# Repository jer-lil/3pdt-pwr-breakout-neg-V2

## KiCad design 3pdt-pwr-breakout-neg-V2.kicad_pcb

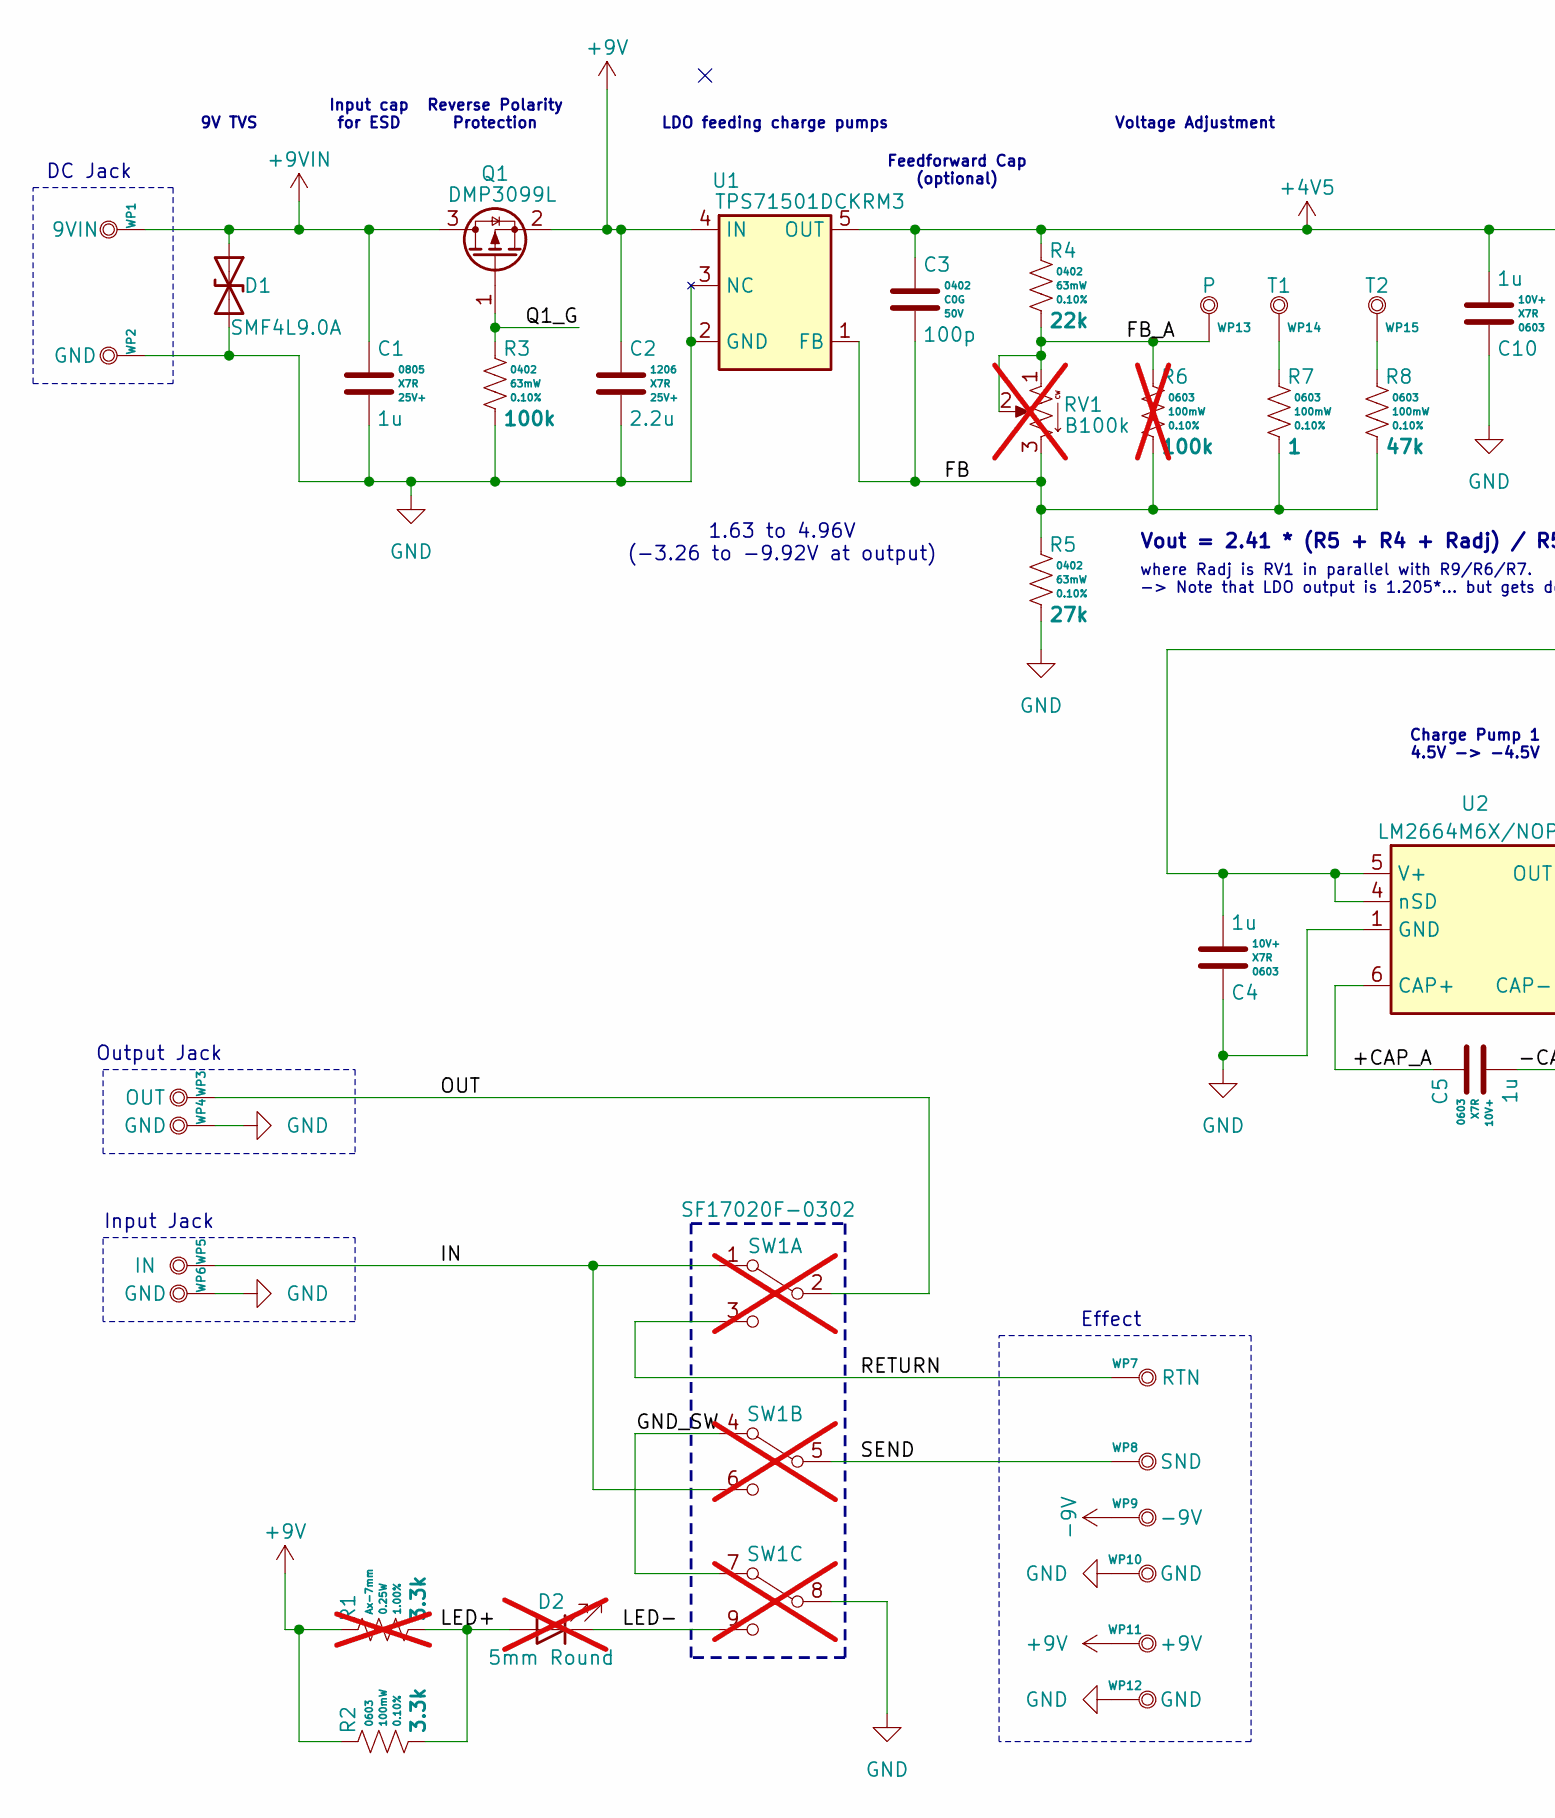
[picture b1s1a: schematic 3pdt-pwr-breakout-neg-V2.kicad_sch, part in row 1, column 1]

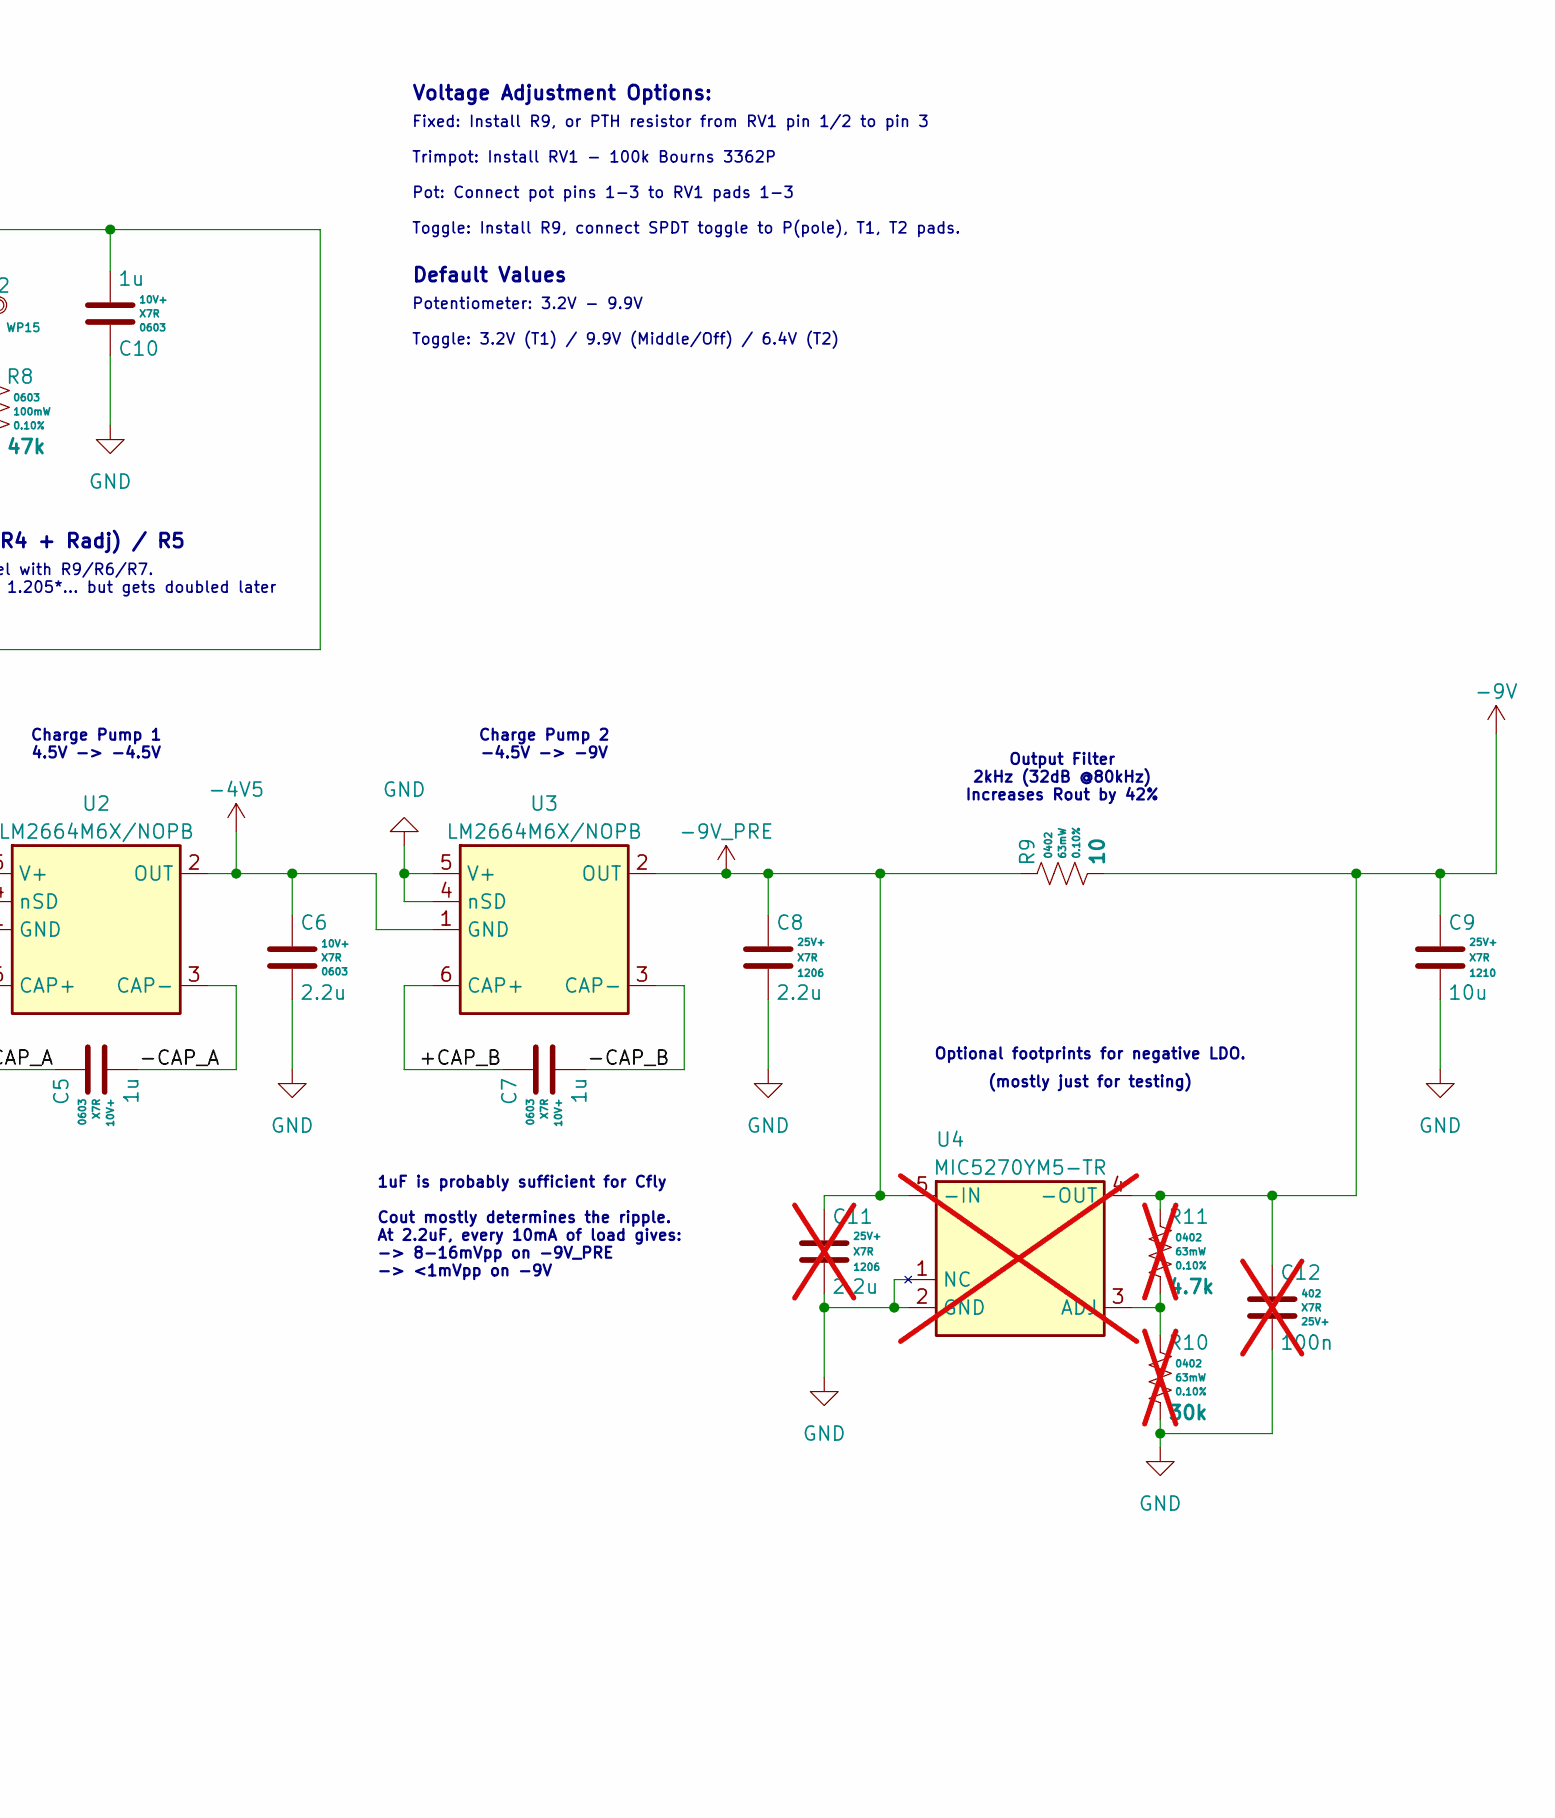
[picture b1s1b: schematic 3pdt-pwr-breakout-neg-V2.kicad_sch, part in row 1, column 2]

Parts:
C1: 1u; C_0805_2012Metric; Voltage 25V+; Tolerance 10%; MPN C0805C105K3RACTU
C2, C8: 2.2u; C_1206_3216Metric; Voltage 25V+; Tolerance 10%; MPN C1206C225K3RACTU
C3: 100p; C_0402_1005Metric; Voltage 50V; Tolerance +/-2%; MPN GRM1555C1H100GA01D
C4, C5, C7, C10: 1u; C_0603_1608Metric; Voltage 10V+; Tolerance 10%; MPN C0603C105K8RACTU
C6: 2.2u; C_0603_1608Metric; Voltage 10V+; Tolerance 10%; MPN C0603C225K8RACTU
C9: 10u; C_1210_3225Metric; Voltage 25V+; Tolerance 10%; MPN C1210C106K3RACTU
C11: 2.2u; C_1206_3216Metric; Voltage 25V+; Tolerance 10%; MPN C1206C225K3RACTU; not fitted
C12: 100n; C_0402_1005Metric; Voltage 25V+; Tolerance 10%; MPN C0402C104K3RACTU; not fitted
D1: SMF4L9.0A; D_SOD-123F; MPN SMF4L9.0A
D2: LED_PTH; LED_D5.0mm_Standoff; not fitted
Q1: DMP3099L; SOT-23; MPN DMP3099L
R1: 3.3k; R_Axial_DIN0207_L6.3mm_D2.5mm_P7.5mm_Horizontal; Tolerance 1.00%; Voltage 250V; MPN MFR-25FBF52-3K3; not fitted
R2: 3.3k; R_0603_1608Metric; Tolerance 0.10%; Voltage 75V; MPN RT0603BRD073K3L
R3: 100k; R_0402_1005Metric; Tolerance 0.10%; Voltage 50V; MPN RT0402BRD07100KL
R4: 22k; R_0402_1005Metric; Tolerance 0.10%; Voltage 50V; MPN RT0402BRD0722KL
R5: 27k; R_0402_1005Metric; Tolerance 0.10%; Voltage 50V; MPN RT0402BRD0727KL
R6: 100k; R_0603_1608Metric; Tolerance 0.10%; Voltage 75V; MPN RT0603BRD07100KL; not fitted
R7: 1; R_0603_1608Metric; Tolerance 0.10%; Voltage 75V; MPN RT0603BRD071RL
R8: 47k; R_0603_1608Metric; Tolerance 0.10%; Voltage 75V; MPN RT0603BRD0747KL
R9: 10; R_0402_1005Metric; Tolerance 0.10%; Voltage 50V; MPN RT0402BRD0710RL
R10: 30k; R_0402_1005Metric; Tolerance 0.10%; Voltage 50V; MPN RT0402BRD0730KL; not fitted
R11: 4.7k; R_0402_1005Metric; Tolerance 0.10%; Voltage 50V; MPN RT0402BRD074K7L; not fitted
RV1: B100k; Potentiometer_Bourns_3362P_Vertical; MPN 3362P-1-104LF; not fitted
SW1: SW_3PDT; SW_STOMP_3PDT; MPN SF17020F-0302; not fitted
U1: TPS71501DCKRM3; SOT-353_SC-70-5; Voltage ADJ; MPN TPS71501DCKRM3
U2, U3: LM2664M6X/NOPB; SOT-23-6; Voltage Ratiometric; MPN LM2664M6X/NOPB
U4: MIC5270YM5-TR; SOT-23-5; Voltage ADJ; MPN MIC5270YM5-TR; not fitted
WP1: 9VIN; WirePad_H0.95mm_22-24AWG
WP2, WP4, WP6, WP10, WP12: GND; WirePad_H0.95mm_22-24AWG
WP3: OUT; WirePad_H0.95mm_22-24AWG
WP5: IN; WirePad_H0.95mm_22-24AWG
WP7: RTN; WirePad_H0.95mm_22-24AWG
WP8: SND; WirePad_H0.95mm_22-24AWG
WP9: -9V; WirePad_H0.95mm_22-24AWG
WP11: +9V; WirePad_H0.95mm_22-24AWG
WP13: P; WirePad_H0.95mm_22-24AWG
WP14: T1; WirePad_H0.95mm_22-24AWG
WP15: T2; WirePad_H0.95mm_22-24AWG

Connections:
+4V5: C3.1, C4.2, C10.2, R4.1, U1.5 (OUT), U2.4 (nSD), U2.5 (V+)
+9V: C2.1, Q1.2 (S), R1.1, R2.1, U1.4 (IN), WP11.1
+9VIN: C1.1, D1.1 (A1), Q1.3 (D), WP1.1
-4V5: C6.2, U2.2 (OUT), U3.1 (GND)
-9V: C9.1, C12.1, R9.2, R11.1, U4.4 (-OUT), WP9.1
-9V_PRE: C8.1, C11.1, R9.1, U3.2 (OUT), U4.5 (-IN)
/+CAP_A: C5.1, U2.6 (CAP+)
/+CAP_B: C7.1, U3.6 (CAP+)
/-CAP_A: C5.2, U2.3 (CAP-)
/-CAP_B: C7.2, U3.3 (CAP-)
/FB: C3.2, R5.1, R6.2, R7.2, R8.2, RV1.3, U1.1 (FB)
/FB_A: R4.2, R6.1, RV1.1, RV1.2, WP13.1
/GND_SW: SW1.4 (A), SW1.7 (A)
/IN: SW1.1 (A), SW1.6 (C), WP5.1
/LED+: D2.2 (A), R1.2, R2.2
/LED-: D2.1 (K), SW1.9 (C)
/OUT: SW1.2 (B), WP3.1
/Q1_G: Q1.1 (G), R3.1
/RETURN: SW1.3 (C), WP7.1
/SEND: SW1.5 (B), WP8.1
GND: C1.2, C2.2, C4.1, C6.1, C8.2, C9.2, C10.1, C11.2, C12.2, D1.2 (A2), R3.2, R5.2, R10.2, SW1.8 (B), U1.2 (GND), U1.3 (NC), U2.1 (GND), U3.4 (nSD), U3.5 (V+), U4.1 (NC), U4.2 (GND), WP2.1, WP4.1, WP6.1, WP10.1, WP12.1
unnamed: R7.1, WP14.1
unnamed: R8.1, WP15.1
unnamed: R10.1, R11.2, U4.3 (ADJ)

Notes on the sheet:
Default Values
Optional footprints for negative LDO.
Voltage Adjustment
where Radj is RV1 in parallel with R9/R6/R7. -> Note that LDO output is 1.205*... but gets doubled later
Reverse Polarity Protection
Effect
DC Jack
Input cap for ESD
Feedforward Cap (optional)
Voltage Adjustment Options:
Fixed: Install R9, or PTH resistor from RV1 pin 1/2 to pin 3 Trimpot: Install RV1 - 100k Bourns 3362P Pot: Connect pot pins 1-3 to RV1 pads 1-3 Toggle: Install R9, connect SPDT toggle to P(pole), T1, T2 pads.
9V TVS
1.63 to 4.96V (-3.26 to -9.92V at output)
Vout = 2.41 * (R5 + R4 + Radj) / R5
LDO feeding charge pumps
Charge Pump 1 4.5V -> -4.5V
Output Filter 2kHz (32dB @80kHz) Increases Rout by 42%
Charge Pump 2 -4.5V -> -9V
1uF is probably sufficient for Cfly Cout mostly determines the ripple. At 2.2uF, every 10mA of load gives: -> 8-16mVpp on -9V_PRE -> <1mVpp on -9V
Potentiometer: 3.2V - 9.9V Toggle: 3.2V (T1) / 9.9V (Middle/Off) / 6.4V (T2)
Output Jack
Input Jack
(mostly just for testing)

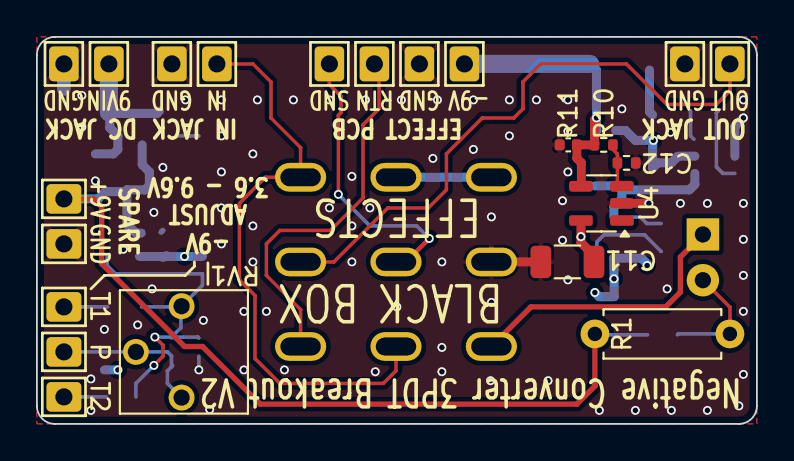
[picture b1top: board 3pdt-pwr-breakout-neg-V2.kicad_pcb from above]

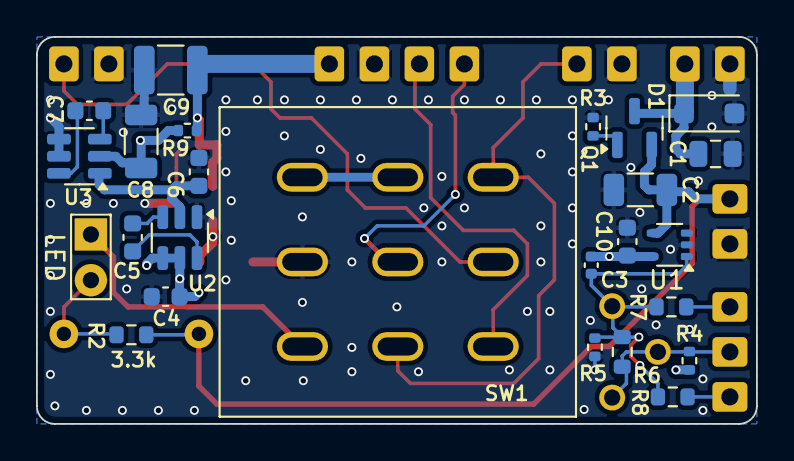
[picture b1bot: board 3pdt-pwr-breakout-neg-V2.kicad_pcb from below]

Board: 4 copper layers, 40.0 x 21.5 mm, 47 parts (25 on the bottom side), 24 nets.

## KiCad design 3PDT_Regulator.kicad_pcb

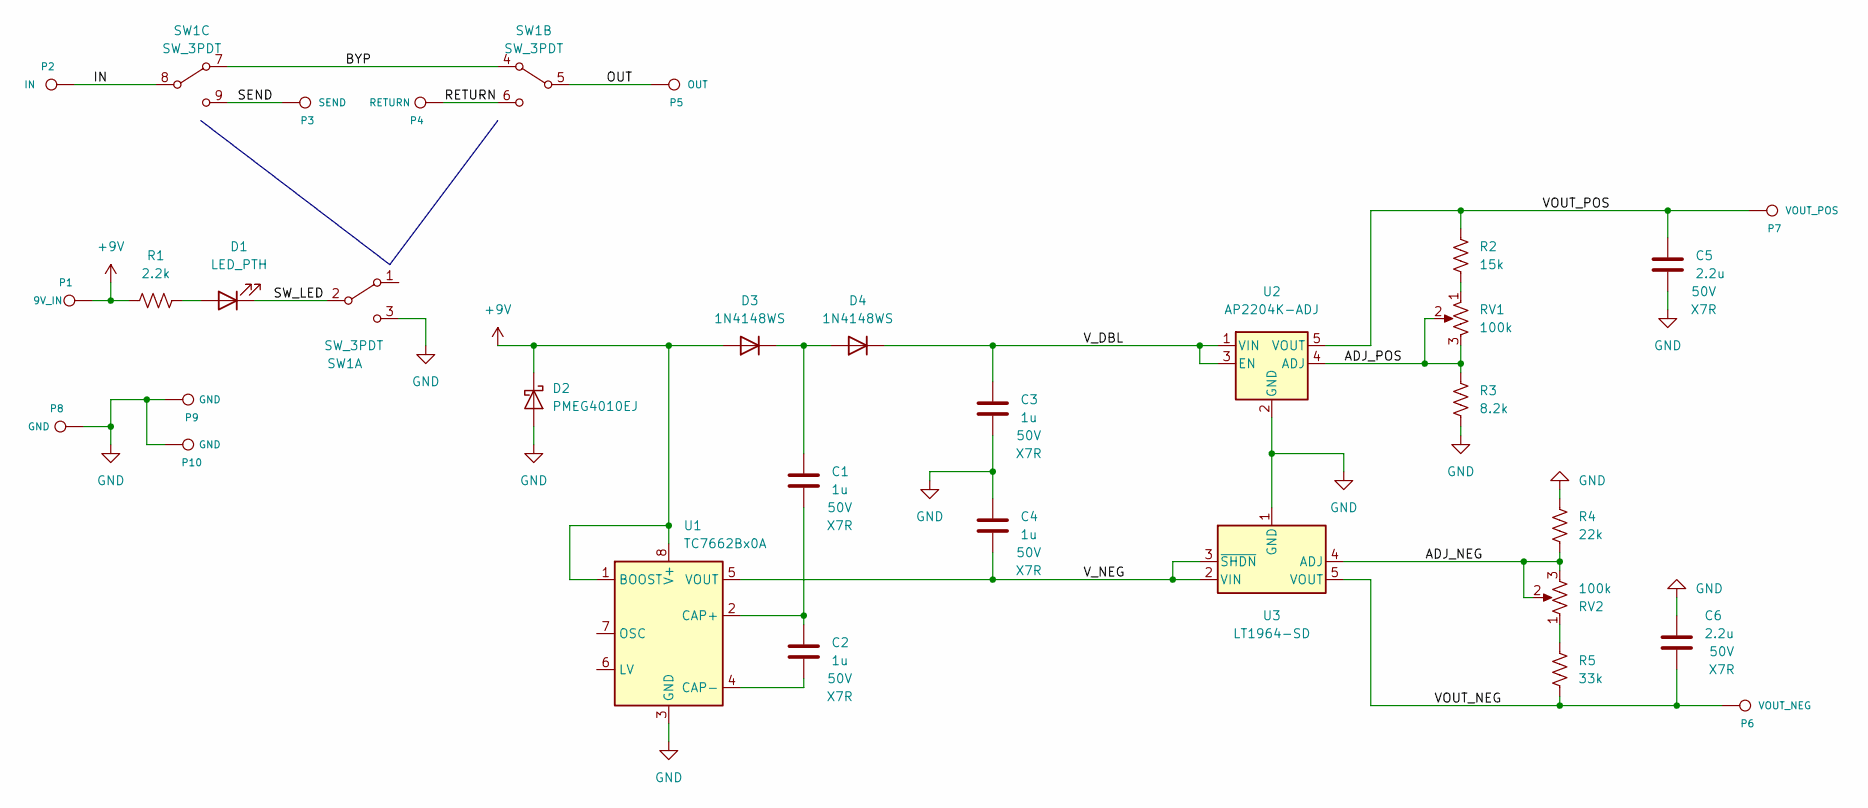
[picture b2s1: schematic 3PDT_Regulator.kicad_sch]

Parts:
C1, C2, C3, C4: 1u; C_0805_2012Metric; Voltage Rating 50V
C5, C6: 2.2u; C_0805_2012Metric; Voltage Rating 50V
D1: LED_PTH; LED_D5.0mm
D2: PMEG4010EJ; D_SOD-323F
D3, D4: 1N4148WS; D_SOD-323
P1: 9V_IN; WirePad_22AWG
P2: IN; WirePad_22AWG
P3: SEND; WirePad_22AWG
P4: RETURN; WirePad_22AWG
P5: OUT; WirePad_22AWG
P6: VOUT_NEG; WirePad_22AWG
P7: VOUT_POS; WirePad_22AWG
P8, P9, P10: GND; WirePad_22AWG
R1: 2.2k; R_0603_1608Metric
R2: 15k; R_0603_1608Metric
R3: 8.2k; R_0603_1608Metric
R4: 22k; R_0603_1608Metric
R5: 33k; R_0603_1608Metric
RV1, RV2: 100k; Potentiometer_Bourns_3386F_Vertical
SW1: SW_3PDT; SW_STOMP_3PDT
U1: TC7662Bx0A; SOIC-8_3.9x4.9mm_P1.27mm
U2: AP2204K-ADJ; SOT-23-5
U3: LT1964-SD; TSOT-23-5

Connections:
+9V: D2.1 (K), D3.2 (A), P1.1, R1.1, U1.1 (BOOST), U1.8 (V+)
/ADJ_NEG: R4.2, RV2.2, RV2.3, U3.4 (ADJ)
/ADJ_POS: R3.2, RV1.2, RV1.3, U2.4 (ADJ)
/BYP: SW1.4 (A), SW1.7 (A)
/IN: P2.1, SW1.8 (B)
/OUT: P5.1, SW1.5 (B)
/RETURN: P4.1, SW1.6 (C)
/SEND: P3.1, SW1.9 (C)
/SW_LED: D1.1 (K), SW1.2 (B)
/VOUT_NEG: C6.2, P6.1, R5.2, U3.5 (VOUT)
/VOUT_POS: C5.1, P7.1, R2.2, U2.5 (VOUT)
/V_DBL: C3.1, D4.1 (K), U2.1 (VIN), U2.3 (EN)
/V_NEG: C4.2, U1.5 (VOUT), U3.2 (VIN), U3.3 (~SHDN)
GND: C3.2, C4.1, C5.2, C6.1, D2.2 (A), P8.1, P9.1, P10.1, R3.1, R4.1, SW1.3 (C), U1.3 (GND), U2.2 (GND), U3.1 (GND)
unnamed: C1.1, D3.1 (K), D4.2 (A)
unnamed: C1.2, C2.1, U1.2 (CAP+)
unnamed: C2.2, U1.4 (CAP-)
unnamed: D1.2 (A), R1.2
unnamed: R2.1, RV1.1
unnamed: R5.1, RV2.1

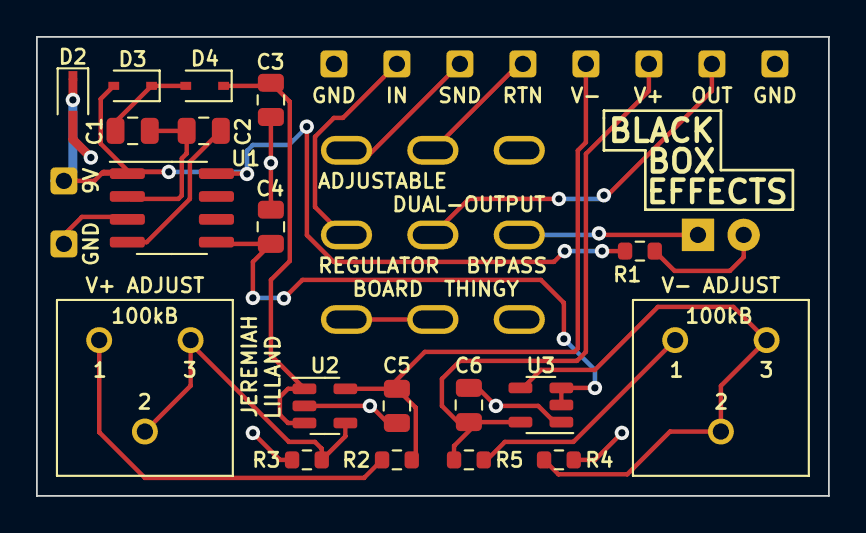
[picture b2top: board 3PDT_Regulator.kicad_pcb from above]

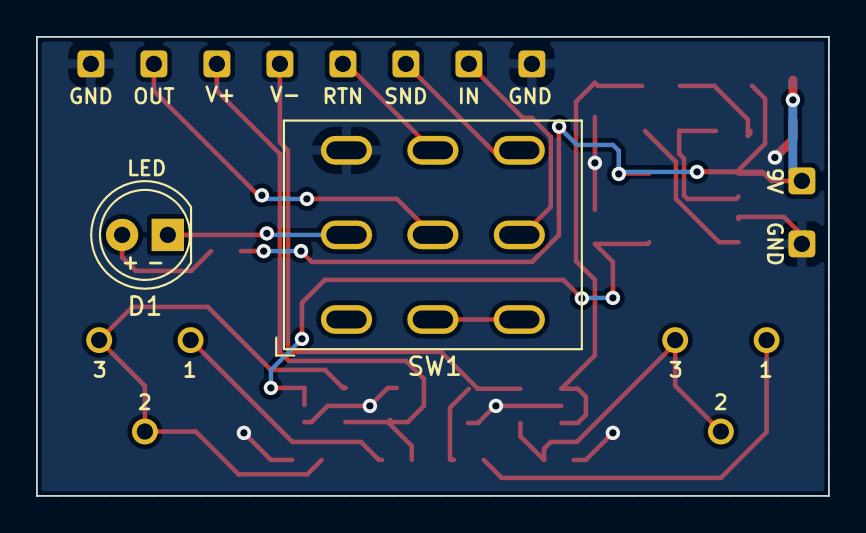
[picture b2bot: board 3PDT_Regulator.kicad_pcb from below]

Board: 2 copper layers, 44.0 x 25.5 mm, 31 parts (6 on the bottom side), 20 nets.

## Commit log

2025-05-20 Finished layout, needs review
    no DRC yet
2025-05-29 Updated R amd C symbols
    Changed field sizes/visibilities. Should pull into PCB too before review
2025-07-24 Moved wire pads, clearing warnings. Good to fab?
2025-10-06 Changed LDO and added negative LDO
    Changed LDO to a leaded package and added an optional negative LDO. Layout changes implemented, going to review and order.
2025-10-06 Generated fab files
2025-10-06 layout stuff
